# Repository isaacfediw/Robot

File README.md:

# Robot
A robot I am building that will follow you around

## Modes
### Auto Mode
**Overview**  
In auto mode the robot is designed to track the position of the transmitter and go to it.  
The DWM3000 can provide highly accurate and precise measurements when done correctly. The  
method I used for finding the distance between the robot (receiver) and the transmitter is known as  
double-sided two-way ranging. After calculating the distance I apply a lowpass fir filter to it using  
a hamming window with 31 taps. Once the distance is calculated the robot pivots itself slightly to the  
left and measures the distance again. It takes note of when the distance is incrementing. If the distance  
starts to decrement after it has already been noticed to increment the robot knows that the position before  
the last slight left pivot must be when the receiver antenna is angled farthest away from the transmitter  
antenna. This works because the receiver antenna is mounted near the end of the robot chassis.  

The problem with my current setup is that my distance measurements are not precise nor accurate when the  
receiver is mounted on the robot chassis. This is because the DWM3000 antennas are vertically polarized,  
which means they will communicate with the lowest amount of noise when they are both on the XZ plane.  
Although slightly more noisy (with introduced nulls), if both antenna are positioned on the XY plane,  
perpendicular to each other, the measurements are still relatively accurate and precise. For the time  
being (while in their respective chassis), the transmitter antenna is positioned on the XY plane and the  
receiver antenna is positioned on the YZ plane. This makes the measurements significantly inaccurate and  
imprecise, preventing auto mode from correctly working. My hope is to redesign the robot chassis to   
support ideally an antenna which is positioned on the XY plane but at the least on a 45 degree angle  
between the XY and YZ planes.  

**How double-sided two-way ranging works**  
6 timestamps are measured: t1 (measured when the transmitter  
sends the first frame), t2 (measured when the receiver receives that first frame), t3  
(measured when the receiver sends its first response), t4 (measured when the transmitter  
receives the receiver's first response), t5 (measured when the transmitter sends the second  
frame), and t6 (measured when the receiver receives that second frame).  

From the 6 timestamps, 4 time values are calculated. The round trip time for the first frame,  
the round trip time for the second frame, the reply time for the first frame, and the reply  
time for the second frame. The time of flight (tof) then calculated as:  
(round trip 1 * round trip 2 - reply 1 * reply 2) / (round trip 1 + round trip 2 + reply 1 + reply 2)  

<details> 
  <summary> For the proof on why the tof equation works click here </summary>

### DS-TWR Time-of-Flight Derivation
#### 1. Numerator Expansion:
$$
\begin{aligned}
\mathrm{tof\_num} &= R_1 R_2 - D_1 D_2 \\
&= (2T + D_1)(2T + D_2) - D_1 D_2 \\
&= 4T^2 + 2T D_2 + 2T D_1 + D_1 D_2 - D_1 D_2 \\
&= 4T^2 + 2T(D_1 + D_2) \\
&= 2T(2T + D_1 + D_2)
\end{aligned}
$$

#### 2. Denominator Expansion:
$$
\begin{aligned}
\mathrm{tof\_denom} &= R_1 + R_2 + D_1 + D_2 \\
&= (2T + D_1) + (2T + D_2) + D_1 + D_2 \\
&= 4T + 2D_1 + 2D_2 \\
&= 2(2T + D_1 + D_2)
\end{aligned}
$$

#### 3. Final Division and Cancellation:
$$
\begin{aligned}
\text{tof} &= \frac{\mathrm{tof\_num}}{\mathrm{tof\_denom}} \\
&= \frac{2T(2T + D_1 + D_2)}{2(2T + D_1 + D_2)} \\
&= \frac{2T}{2} \\
&= T
\end{aligned}
$$

</details>

We then multiply the time of flight by 15.65E-12 to get from DWT system time to seconds.  
Finally, to calculate the distance (in cm) the tof in seconds is multiplied by 100 times  
times the speed of light.  

### Manual Mode
**Overview**  
In manual mode the user has full control over the robot by using the joystick on the transmitter.  
The RP2040-Zero features a 12 bit adc, but I limit the range to 0 to 800 and then shift it by  
540 to make the rest position 0, the low position -240, and the highest position +260, in both  
x and y directions. I implemented a software deadzone of 50 adc values to prevent unwanted drifting  
when in manual mode.  
  
**How the direction and speed is decided**  
I compare the x and y adc value. If x > y then we want to turn the robot, otherwise we want to move  
forward or backward. If we are turning and x > 0 we want to go left, otherwise we go right. If we are  
not turning and y > 0 we want to go forwards, otherwise we go backwards. The amount of steps we want the  
robot to take is calculated by mapping the adc value to a steps value, using -240 and +260 as the adc range    
and 10 and 100 as the step range. This information is then sent to the robot in 3 bytes. (0xAB to indicate  
manual mode, a direction byte, and the number of steps as the final byte).

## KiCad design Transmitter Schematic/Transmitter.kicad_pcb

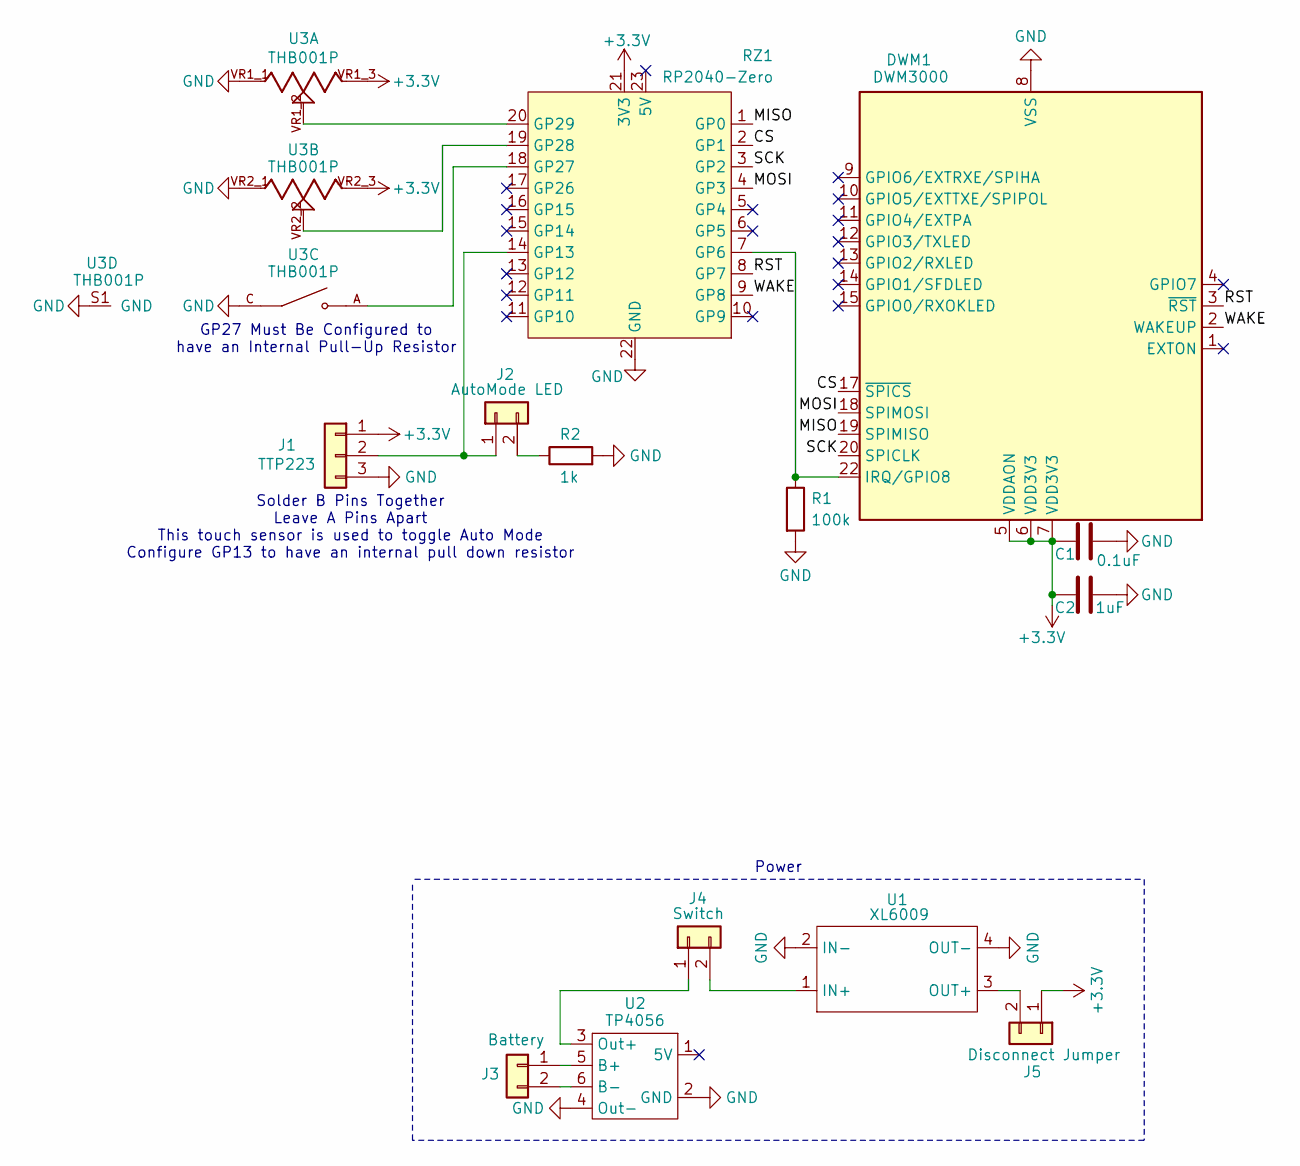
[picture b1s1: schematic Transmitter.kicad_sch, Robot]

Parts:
C1: 0.1uF; C_0805_2012Metric
C2: 1uF; C_0805_2012Metric
DWM1: DWM3000; DWM1000; MPN DWM3000.E1.1SR
J1: TTP223; PinSocket_1x03_P2.54mm_Vertical
J2: AutoMode LED; PinSocket_1x02_P2.54mm_Vertical
J3: Battery; PinSocket_1x02_P2.54mm_Vertical
J4: Switch; PinSocket_1x02_P2.54mm_Vertical
J5: Disconnect Jumper; PinSocket_1x02_P2.54mm_Vertical
R1: 100k; R_0805_2012Metric_Pad1.20x1.40mm_HandSolder
R2: 1k; R_0805_2012Metric_Pad1.20x1.40mm_HandSolder
RZ1: RP2040-Zero
U1: XL6009
U2: TP4056; TP4056-18650
U3: THB001P; CNK_THB001P; PARTREV 27 Jan 22

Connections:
+3.3V: C1.1, C2.1, DWM1.5 (VDDAON), DWM1.6 (VDD3V3), DWM1.7 (VDD3V3), J1.1, J5.1, RZ1.21 (3V3), U3.VR1_3, U3.VR2_3
/CS: DWM1.17 (~SPICS), RZ1.2 (GP1)
/MISO: DWM1.19 (SPIMISO), RZ1.1 (GP0)
/MOSI: DWM1.18 (SPIMOSI), RZ1.4 (GP3)
/RST: DWM1.3 (~RST), RZ1.8 (GP7)
/SCK: DWM1.20 (SPICLK), RZ1.3 (GP2)
/WAKE: DWM1.2 (WAKEUP), RZ1.9 (GP8)
GND: C1.2, C2.2, DWM1.8 (VSS), DWM1.16 (VSS), DWM1.21 (VSS), DWM1.23 (VSS), DWM1.24 (VSS), J1.3, R1.2, R2.2, RZ1.22 (GND), U1.2 (IN-), U1.4 (OUT-), U2.2 (GND), U2.4 (Out-), U3.C, U3.D, U3.S1 (GND), U3.S2, U3.S3, U3.S4, U3.VR1_1, U3.VR2_1
unnamed: DWM1.22 (IRQ/GPIO8), R1.1, RZ1.7 (GP6)
unnamed: J1.2, J2.1, RZ1.14 (GP13)
unnamed: J2.2, R2.1
unnamed: J3.1, U2.5 (B+)
unnamed: J3.2, U2.6 (B-)
unnamed: J4.1, U2.3 (Out+)
unnamed: J4.2, U1.1 (IN+)
unnamed: J5.2, U1.3 (OUT+)
unnamed: RZ1.18 (GP27), U3.A, U3.B
unnamed: RZ1.19 (GP28), U3.VR2_2
unnamed: RZ1.20 (GP29), U3.VR1_2

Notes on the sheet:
GP27 Must Be Configured to have an Internal Pull-Up Resistor
Power
Solder B Pins Together Leave A Pins Apart This touch sensor is used to toggle Auto Mode Configure GP13 to have an internal pull down resistor

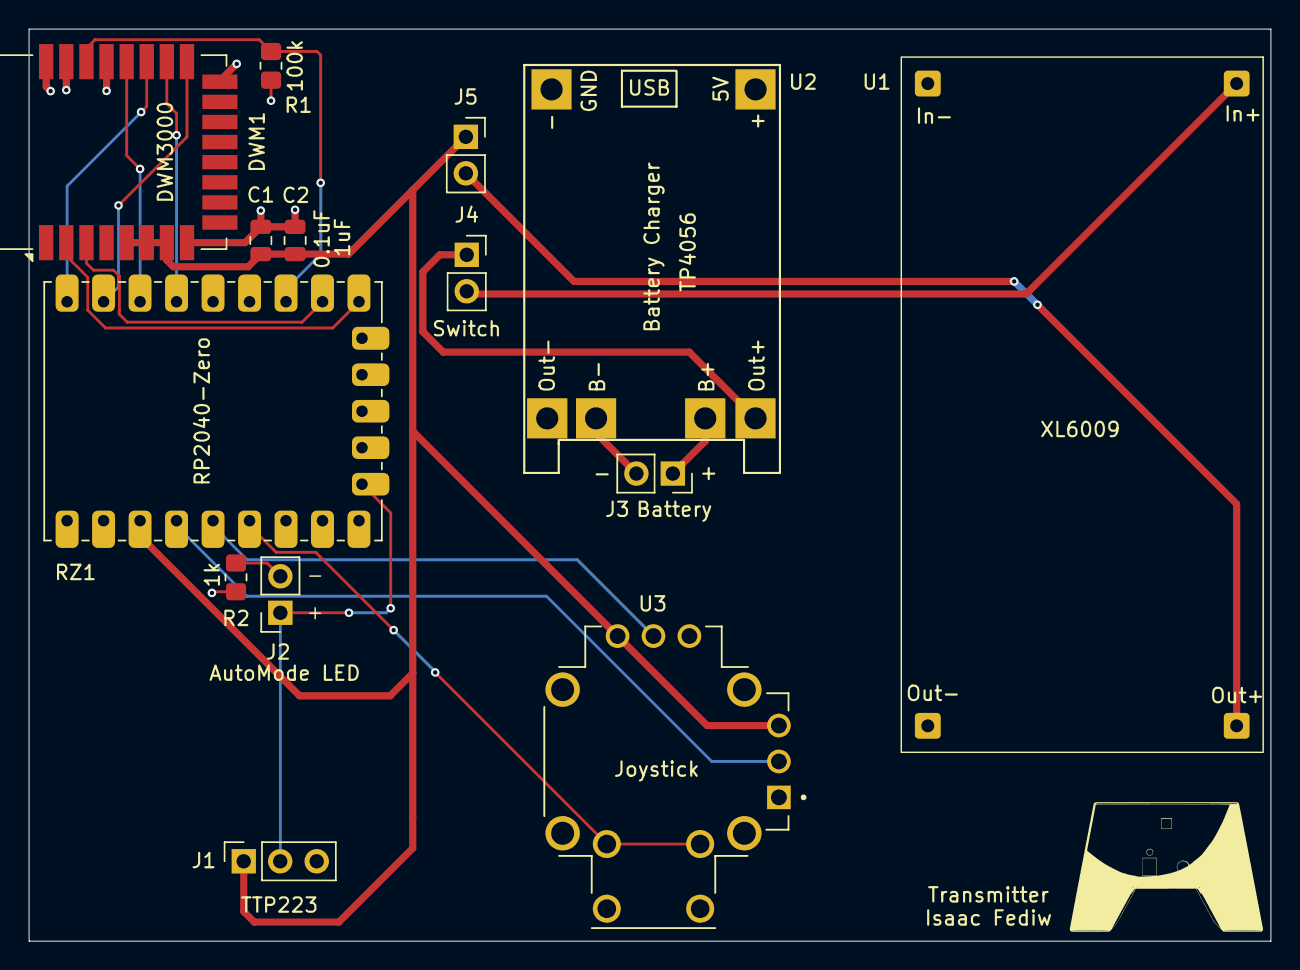
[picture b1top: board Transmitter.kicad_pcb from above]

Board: 2 copper layers, 86.4 x 63.5 mm, 14 parts (0 on the bottom side), 19 nets.

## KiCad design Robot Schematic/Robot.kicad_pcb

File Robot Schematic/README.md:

# Robot
A robot I am designing that follows you around

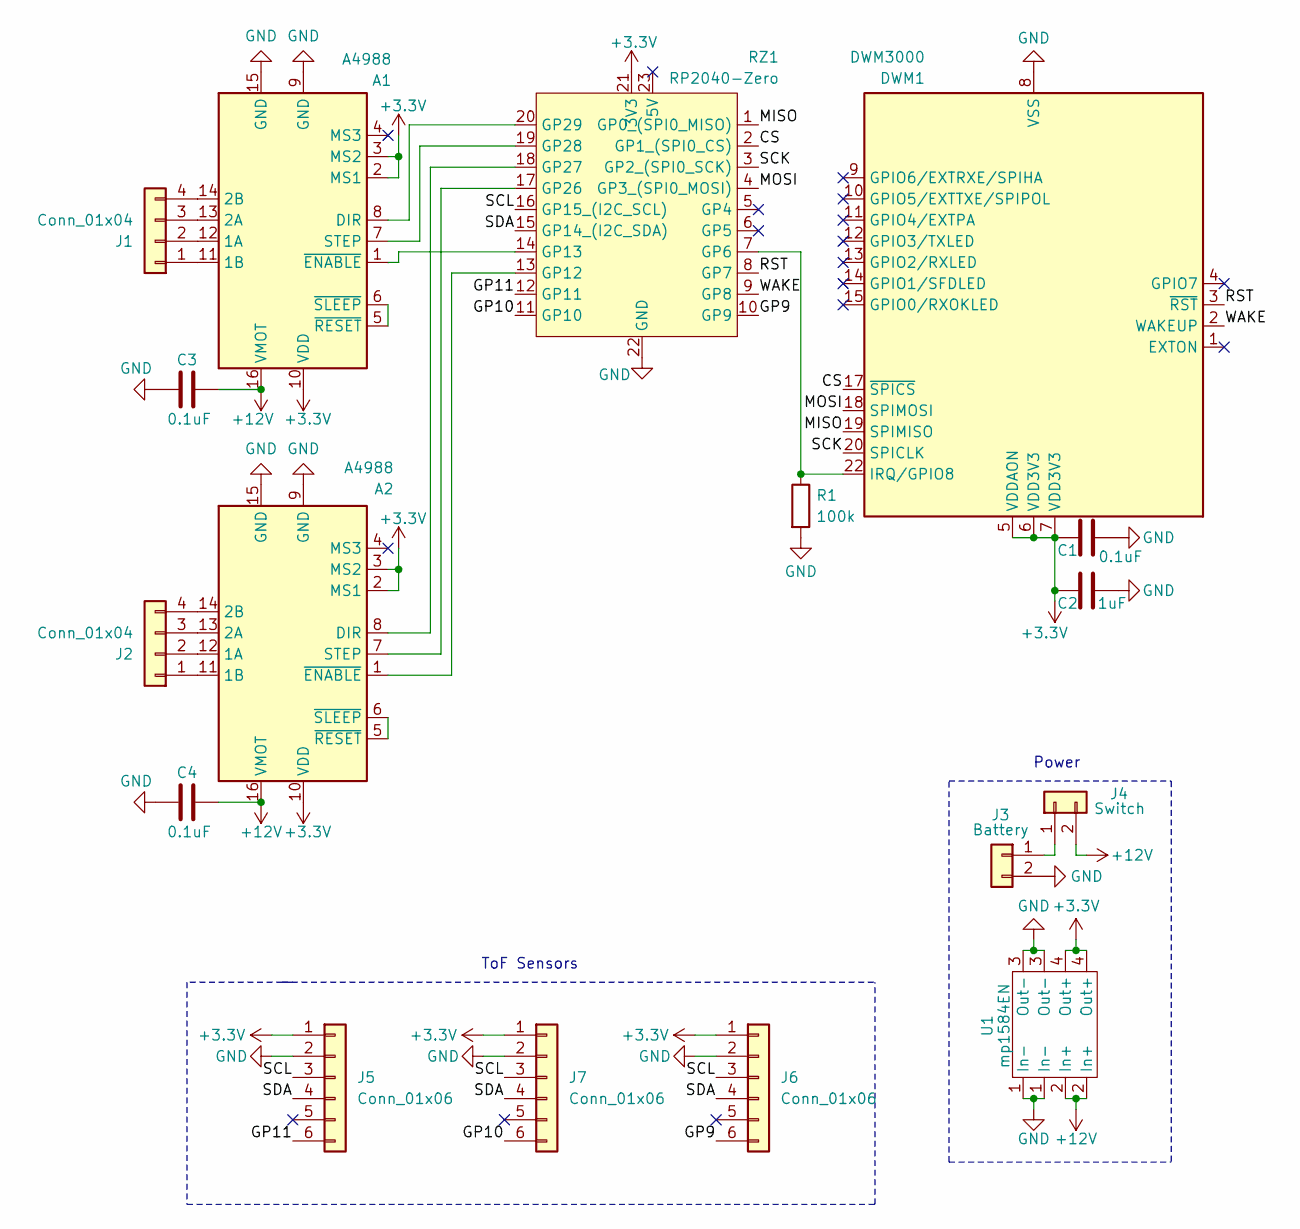
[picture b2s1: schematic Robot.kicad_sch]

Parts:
A1, A2: A4988
C1, C3, C4: 0.1uF; C_0805_2012Metric
C2: 1uF; C_0805_2012Metric
DWM1: DWM3000; DWM1000; MPN DWM3000.E1.1SR
J1, J2: Conn_01x04; PinSocket_1x04_P2.54mm_Vertical
J3: Battery; PinSocket_1x02_P2.54mm_Vertical
J4: Switch; PinSocket_1x02_P2.54mm_Vertical
J5, J6, J7: Conn_01x06; PinSocket_1x06_P2.54mm_Vertical
R1: 100k; R_0805_2012Metric_Pad1.20x1.40mm_HandSolder
RZ1: RP2040-Zero
U1: mp1584EN; mp158en

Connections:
+3.3V: A1.2 (MS1), A1.3 (MS2), A1.10 (VDD), A2.2 (MS1), A2.3 (MS2), A2.10 (VDD), C1.1, C2.1, DWM1.5 (VDDAON), DWM1.6 (VDD3V3), DWM1.7 (VDD3V3), J5.1, J6.1, J7.1, RZ1.21 (3V3), U1.4 (Out+)
+12V: A1.16 (VMOT), A2.16 (VMOT), C3.1, C4.1, J4.2, U1.2 (In+)
/CS: DWM1.17 (~SPICS), RZ1.2 (GP1_(SPI0_CS))
/GP9: J6.6, RZ1.10 (GP9)
/GP10: J7.6, RZ1.11 (GP10)
/GP11: J5.6, RZ1.12 (GP11)
/MISO: DWM1.19 (SPIMISO), RZ1.1 (GP0_(SPI0_MISO))
/MOSI: DWM1.18 (SPIMOSI), RZ1.4 (GP3_(SPI0_MOSI))
/RST: DWM1.3 (~RST), RZ1.8 (GP7)
/SCK: DWM1.20 (SPICLK), RZ1.3 (GP2_(SPI0_SCK))
/SCL: J5.3, J6.3, J7.3, RZ1.16 (GP15_(I2C_SCL))
/SDA: J5.4, J6.4, J7.4, RZ1.15 (GP14_(I2C_SDA))
/WAKE: DWM1.2 (WAKEUP), RZ1.9 (GP8)
GND: A1.9 (GND), A1.15 (GND), A2.9 (GND), A2.15 (GND), C1.2, C2.2, C3.2, C4.2, DWM1.8 (VSS), DWM1.16 (VSS), DWM1.21 (VSS), DWM1.23 (VSS), DWM1.24 (VSS), J3.2, J5.2, J6.2, J7.2, R1.2, RZ1.22 (GND), U1.1 (In-), U1.3 (Out-)
unnamed: A1.12 (1A), J1.2
unnamed: A1.11 (1B), J1.1
unnamed: A1.13 (2A), J1.3
unnamed: A1.14 (2B), J1.4
unnamed: A1.8 (DIR), RZ1.20 (GP29)
unnamed: A1.7 (STEP), RZ1.19 (GP28)
unnamed: A1.1 (~ENABLE), RZ1.14 (GP13)
unnamed: A1.5 (~RESET), A1.6 (~SLEEP)
unnamed: A2.12 (1A), J2.2
unnamed: A2.11 (1B), J2.1
unnamed: A2.13 (2A), J2.3
unnamed: A2.14 (2B), J2.4
unnamed: A2.8 (DIR), RZ1.18 (GP27)
unnamed: A2.7 (STEP), RZ1.17 (GP26)
unnamed: A2.1 (~ENABLE), RZ1.13 (GP12)
unnamed: A2.5 (~RESET), A2.6 (~SLEEP)
unnamed: DWM1.22 (IRQ/GPIO8), R1.1, RZ1.7 (GP6)
unnamed: J3.1, J4.1

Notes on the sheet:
Power
ToF Sensors

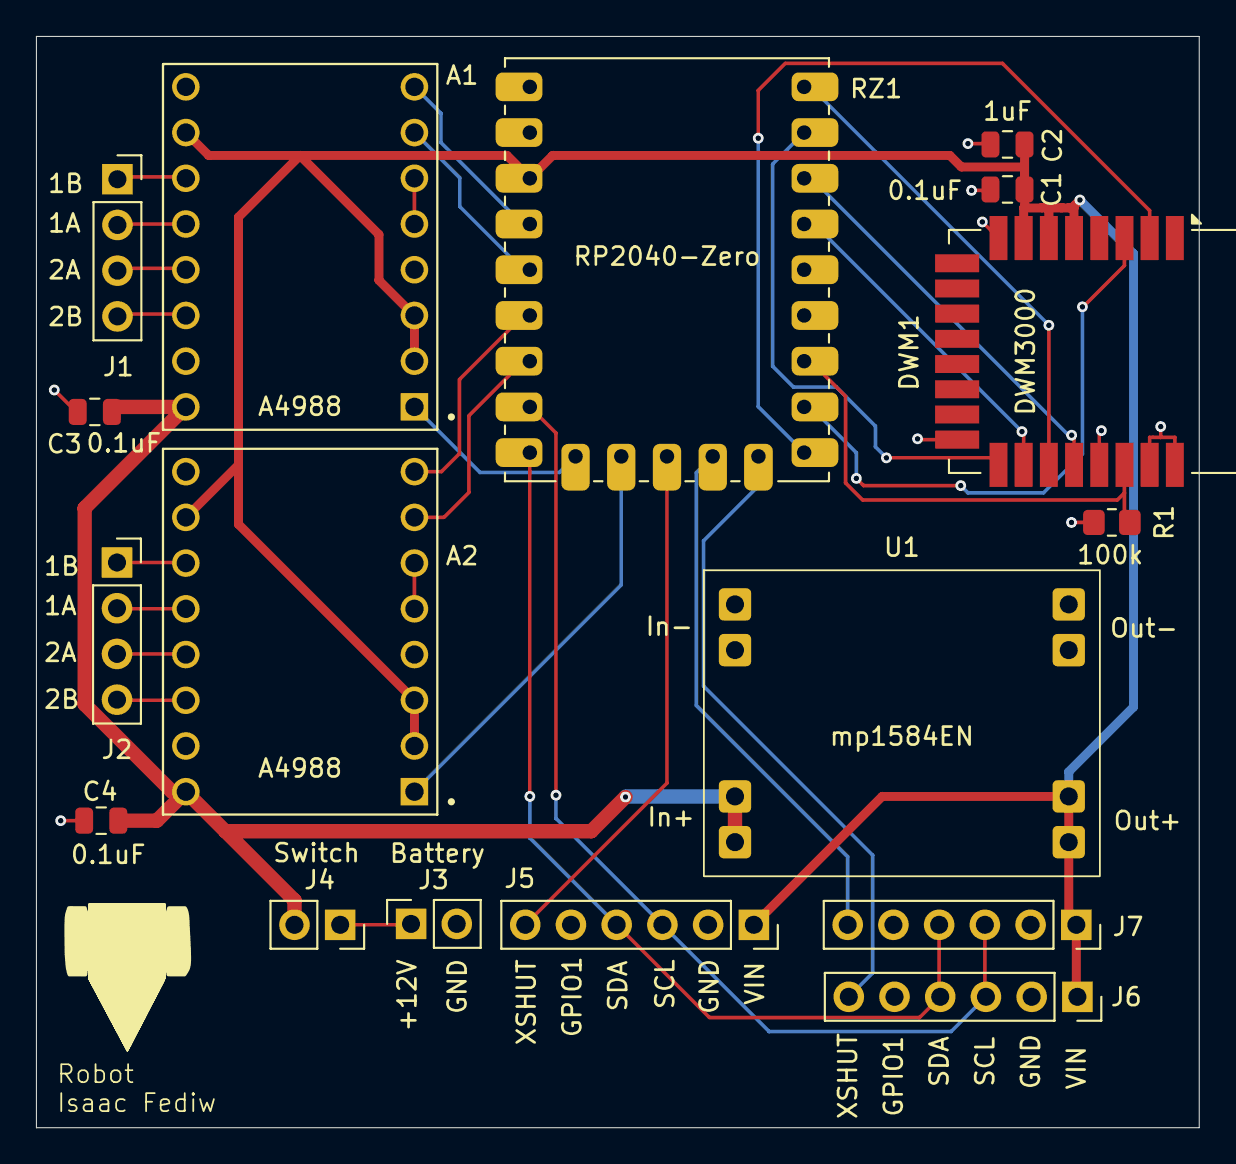
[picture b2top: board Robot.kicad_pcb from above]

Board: 2 copper layers, 64.6 x 60.6 mm, 17 parts (0 on the bottom side), 32 nets.

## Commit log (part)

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2026-03-22 Add Code to this repo
